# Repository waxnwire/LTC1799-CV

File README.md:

# LTC1799 CV
CV controlled LTC1799

This is a circuit schematic, PCB and Gerber files (for creating your own)

LTC1799 Clock - perfect for circuit bending

Unlike other LTC1799 boards out there, this one allows for two CV inputs

Set the base pitch, and then using an LFO or Sequencer, modulate the pitch

# Cost:
while boards from Etsy etc might cost around $10each, but learning how to manufacture the boards yourself, it should cost around the same each (making 5), but with the bonus value of it being a voltage controlled clock!

Donation

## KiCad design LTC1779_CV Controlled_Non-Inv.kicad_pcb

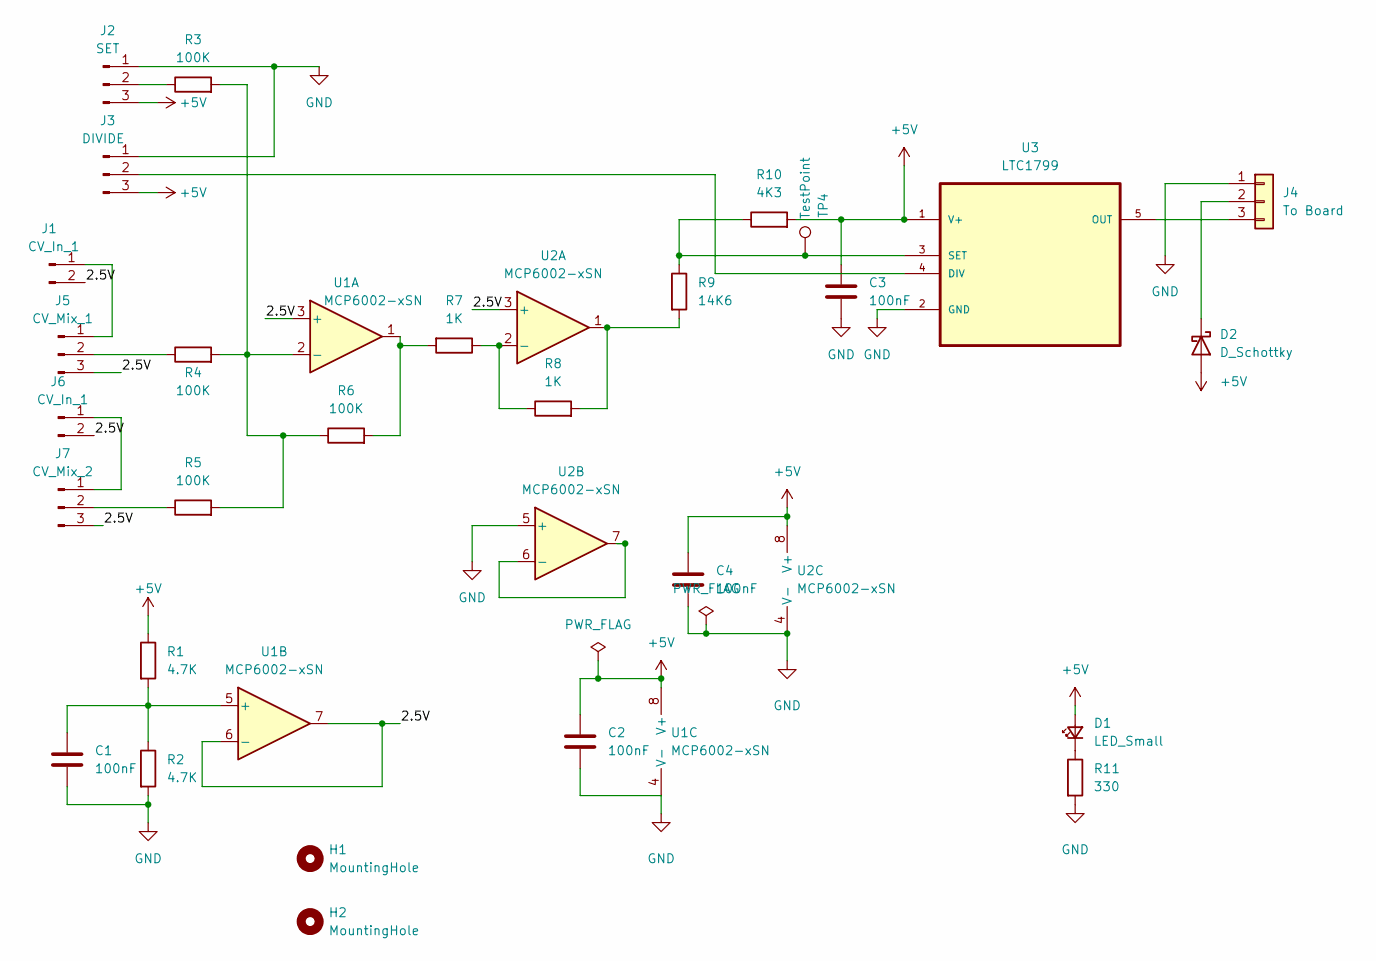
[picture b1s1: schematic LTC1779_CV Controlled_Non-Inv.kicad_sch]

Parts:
C1, C2, C3, C4: 100nF; C_0805_2012Metric_Pad1.18x1.45mm_HandSolder; LCSC C28233
D1: LED_Small; LED_0805_2012Metric_Pad1.15x1.40mm_HandSolder
D2: D_Schottky; D_SMA
H1, H2: MountingHole; MountingHole_2mm
J1, J6: CV_In_1; Molex_KK-254_AE-6410-02A_1x02_P2.54mm_Vertical
J2: SET; Molex_KK-254_AE-6410-03A_1x03_P2.54mm_Vertical
J3: DIVIDE; Molex_KK-254_AE-6410-03A_1x03_P2.54mm_Vertical
J4: To Board; Molex_KK-254_AE-6410-03A_1x03_P2.54mm_Vertical
J5: CV_Mix_1; Molex_KK-254_AE-6410-03A_1x03_P2.54mm_Vertical
J7: CV_Mix_2; Molex_KK-254_AE-6410-03A_1x03_P2.54mm_Vertical
R1, R2: 4.7K; R_0805_2012Metric_Pad1.20x1.40mm_HandSolder; LCSC C17673
R3, R4, R5, R6: 100K; R_0805_2012Metric_Pad1.20x1.40mm_HandSolder; LCSC C149504
R7, R8: 1K; R_0805_2012Metric_Pad1.20x1.40mm_HandSolder; LCSC C17513
R9: 14K6; R_0805_2012Metric_Pad1.20x1.40mm_HandSolder; LCSC C17475
R10: 4K3; R_0805_2012Metric_Pad1.20x1.40mm_HandSolder; LCSC C17673
R11: 330; R_0805_2012Metric_Pad1.20x1.40mm_HandSolder
TP4: TestPoint; TestPoint_THTPad_D2.5mm_Drill1.2mm
U1: MCP6002-xSN
U2: MCP6002-xSN; SOIC-8_3.9x4.9mm_P1.27mm
U3: LTC1799; SOT-23-5; MPN LTC1799CS5#TRMPBF; LCSC C678789

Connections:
+5V: C2.1, C3.1, C4.1, D1.2 (A), D2.2 (A), J2.3, J3.3, R1.1, R10.2, U1.8 (V+), U2.8 (V+), U3.1 (V+)
/2.5V: J1.2, J5.3, J6.2, J7.3, U1.3 (+), U1.6 (-), U1.7, U2.3 (+)
GND: C1.2, C2.2, C3.2, C4.2, J2.1, J3.1, J4.1, R2.2, R11.2, U1.4 (V-), U2.4 (V-), U2.5 (+), U3.2 (GND)
unnamed: D1.1 (K), R11.1
unnamed: D2.1 (K), J4.2
unnamed: J1.1, J5.1
unnamed: J2.2, R3.1
unnamed: J3.2, U3.4 (DIV)
unnamed: J4.3, U3.5 (OUT)
unnamed: J5.2, R4.1
unnamed: J6.1, J7.1
unnamed: J7.2, R5.1
unnamed: R6.2, R7.2, U1.1
unnamed: R8.2, R9.2, U2.1
unnamed: R3.2, R4.2, R5.2, R6.1, U1.2 (-)
unnamed: C1.1, R1.2, R2.1, U1.5 (+)
unnamed: R7.1, R8.1, U2.2 (-)
unnamed: U2.6 (-), U2.7
unnamed: R9.1, R10.1, TP4.1, U3.3 (SET)

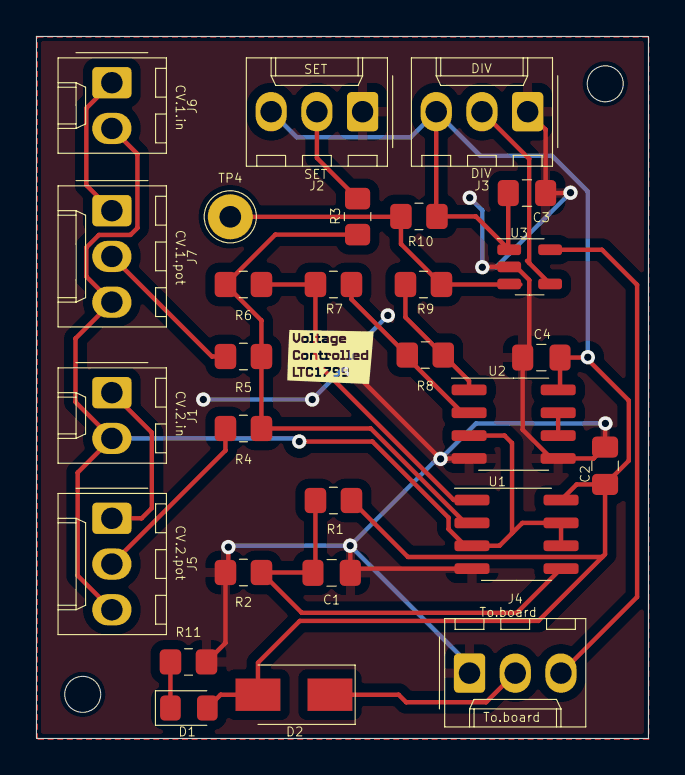
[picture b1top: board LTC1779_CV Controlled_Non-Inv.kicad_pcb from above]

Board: 2 copper layers, 34.0 x 39.0 mm, 30 parts (0 on the bottom side), 19 nets.

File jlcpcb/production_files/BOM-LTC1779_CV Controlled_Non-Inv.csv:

Comment,Designator,Footprint,LCSC,Quantity
100K,"R3,R4,R5,R6",R_0805_2012Metric_Pad1.20x1.40mm_HandSolder,C149504,4
100nF,"C1,C2,C3,C4",C_0805_2012Metric_Pad1.18x1.45mm_HandSolder,C28233,4
14K6,R9,R_0805_2012Metric_Pad1.20x1.40mm_HandSolder,C17475,1
1K,"R7,R8",R_0805_2012Metric_Pad1.20x1.40mm_HandSolder,C17513,2
330,R11,R_0805_2012Metric_Pad1.20x1.40mm_HandSolder,C17630,1
4.7K,"R1,R2",R_0805_2012Metric_Pad1.20x1.40mm_HandSolder,C17673,2
4K3,R10,R_0805_2012Metric_Pad1.20x1.40mm_HandSolder,C17667,1
D_Schottky,D2,D_SMA,C28646298,1
LED_Small,D1,LED_0805_2012Metric_Pad1.15x1.40mm_HandSolder,C2296,1
LTC1799,U3,SOT-23-5,C678789,1
MCP6002-xSN,"U1,U2",SOIC-8_3.9x4.9mm_P1.27mm,C7377,2
CV_Mix_1,J5,Molex_KK-254_AE-6410-03A_1x03_P2.54mm_Vertical,,1
DIVIDE,J3,Molex_KK-254_AE-6410-03A_1x03_P2.54mm_Vertical,,1
TestPoint,TP4,TestPoint_THTPad_D2.5mm_Drill1.2mm,,1
CV_In_1,J6,Molex_KK-254_AE-6410-02A_1x02_P2.54mm_Vertical,,1
SET,J2,Molex_KK-254_AE-6410-03A_1x03_P2.54mm_Vertical,,1
MountingHole,H1,MountingHole_2mm,,1
MountingHole,H2,MountingHole_2mm,,1
CV_In_1,J1,Molex_KK-254_AE-6410-02A_1x02_P2.54mm_Vertical,,1
CV_Mix_2,J7,Molex_KK-254_AE-6410-03A_1x03_P2.54mm_Vertical,,1
To Board,J4,Molex_KK-254_AE-6410-03A_1x03_P2.54mm_Vertical,,1

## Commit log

2026-05-11 sharing the LTC1799 files
2026-05-21 added a logo
